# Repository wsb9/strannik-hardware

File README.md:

Hardware sources of Strannik, ortholinear wireless keyboard.

ZMK config is in [peer software repo](https://github.com/wsb9/strannik).

# About

This project inspired by awesome [ZSA Moonlander](https://www.zsa.io/moonlander). 
At the time of start, ZSA guys haven't yet made Voyager, and I wanted very similar 
low profile wireless keyboard, so, this project had a great initial kick.

It currently uses Kailh Choc low profile switches, [NiceNano](https://nicekeyboards.com/nice-nano) as its brain and [ZMK](https://zmk.dev/) as firmware.

Current plan is to make project usable in daily use (instead of cardboard wired prototype).

# Future plans

There's few ideas:

 - make even thinner keeb based on Kailh notebook switches
 - create version with large batteries and backlight
 - probably create version with encoder on the edge

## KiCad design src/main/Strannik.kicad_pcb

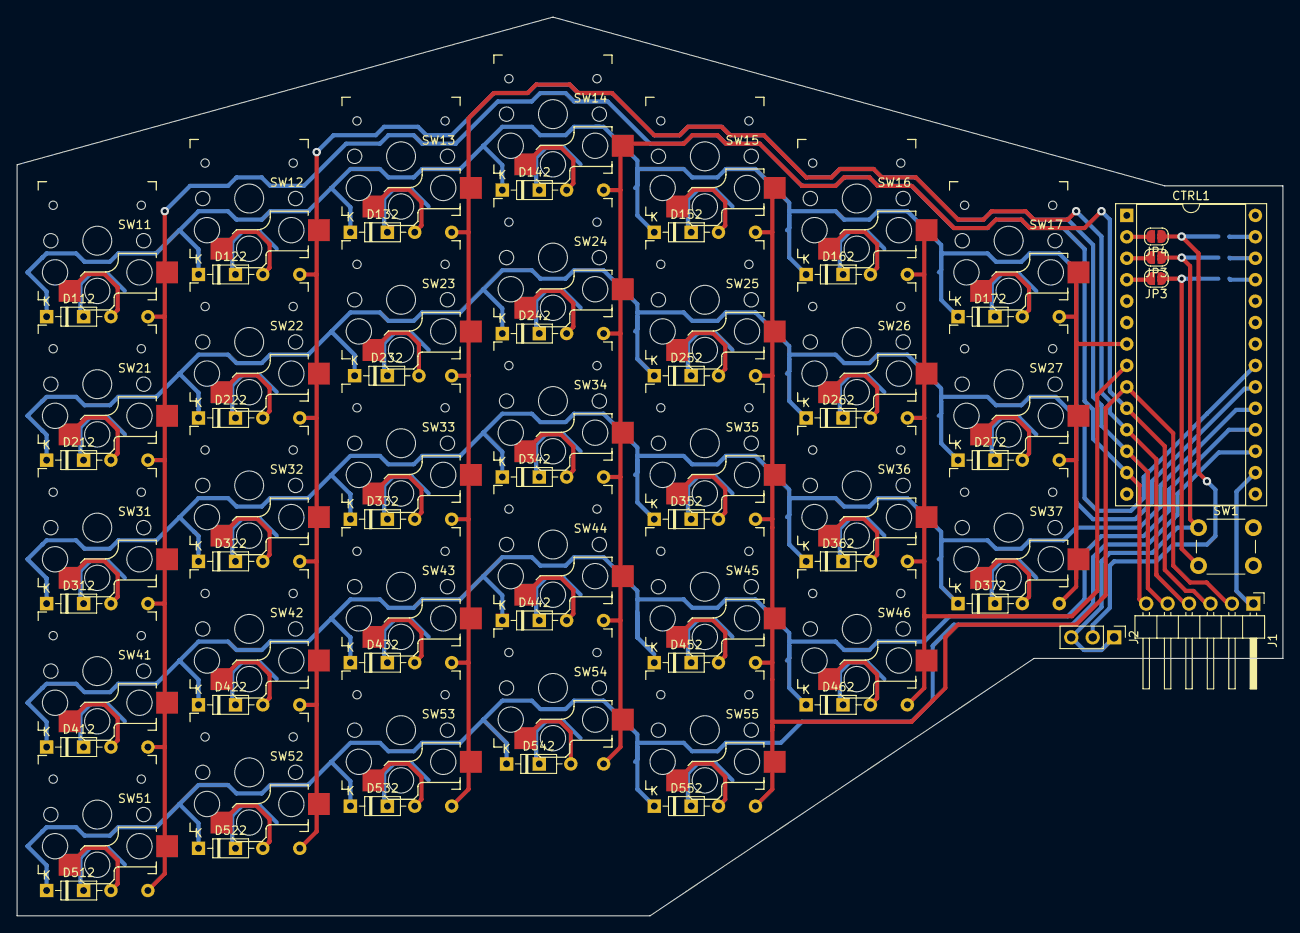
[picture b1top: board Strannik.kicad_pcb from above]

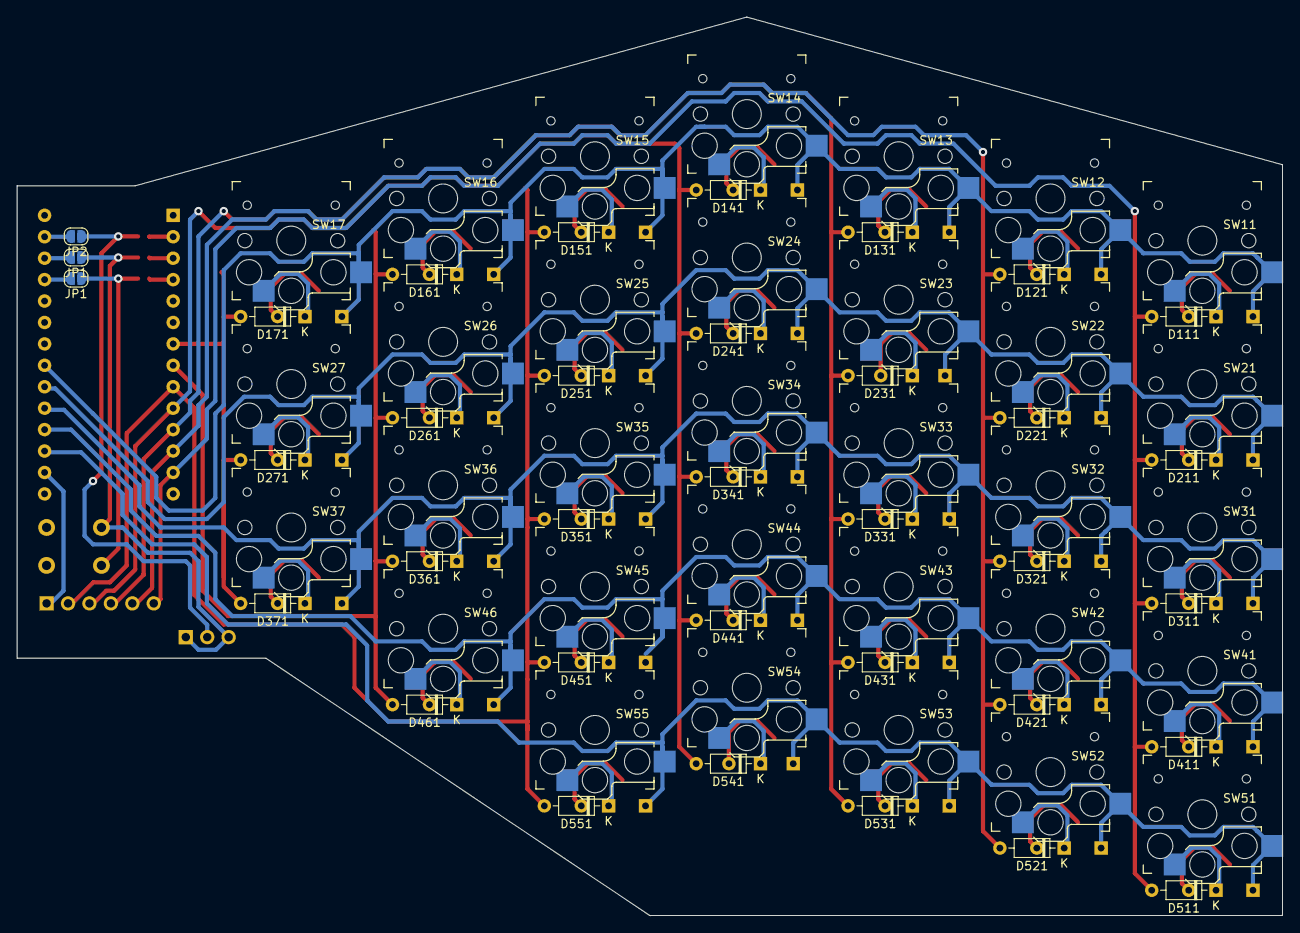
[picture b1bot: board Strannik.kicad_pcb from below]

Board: 2 copper layers, 150.0 x 106.5 mm, 106 parts (35 on the bottom side), 85 nets.

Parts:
CTRL1: Nice Nano; DIP-28_W15.24mm_Socket
D111, D112, D121, D122, D131, D132, D141, D142, D151, D152, D161, D162, D171, D172, D211, D212, D221, D222, D231, D232, D241, D242, D251, D252, D261, D262, D271, D272, D311, D312, D321, D322, D331, D332, D341, D342, D351, D352, D361, D362, D371, D372, D411, D412, D421, D422, D431, D432, D441, D442, D451, D452, D461, D462, D511, D512, D521, D522, D531, D532, D541, D542, D551, D552: 1N4148; D_DO-35_SOD27_P7.62mm_Horizontal
J1: Thumb cluster; PinHeader_1x06_P2.54mm_Horizontal
J2: Battery; PinHeader_1x03_P2.54mm_Vertical
JP1, JP1#2: Ground Left; SolderJumper-2_P1.3mm_Open_RoundedPad1.0x1.5mm
JP2: VCC Left; SolderJumper-2_P1.3mm_Open_RoundedPad1.0x1.5mm
JP3, JP3#2: Ground Right; SolderJumper-2_P1.3mm_Open_RoundedPad1.0x1.5mm
JP4: VCC Right; SolderJumper-2_P1.3mm_Open_RoundedPad1.0x1.5mm
SW1: Reset; SW_PUSH_6mm_H4.3mm
SW11, SW12, SW13, SW14, SW15, SW16, SW17, SW21, SW22, SW23, SW24, SW25, SW26, SW27, SW31, SW32, SW33, SW34, SW35, SW36, SW37, SW41, SW42, SW43, SW44, SW45, SW46, SW51, SW52, SW53, SW54, SW55: SW_Push_Dual; Kailh_socket_PG1350_reversible

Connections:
unnamed: CTRL1.2, JP4.2 (B)
unnamed: CTRL1.3, JP3.2 (B)
unnamed: CTRL1.4, JP3#2.2 (B)
unnamed: CTRL1.7, D171.2 (A), D271.2 (A), D371.2 (A), SW17.4, SW27.4, SW37.4
unnamed: CTRL1.8, D161.2 (A), D261.2 (A), D361.2 (A), D461.2 (A), SW16.4, SW26.4, SW36.4, SW46.4
unnamed: CTRL1.9, D151.2 (A), D251.2 (A), D351.2 (A), D451.2 (A), D551.2 (A), J1.2, SW15.4, SW25.4, SW35.4, SW45.4, SW55.4
unnamed: CTRL1.10, D141.2 (A), D241.2 (A), D341.2 (A), D441.2 (A), D541.2 (A), J1.3, SW14.4, SW24.4, SW34.4, SW44.4, SW54.4
unnamed: CTRL1.11, D131.2 (A), D231.2 (A), D331.2 (A), D431.2 (A), D531.2 (A), J1.4, SW13.4, SW23.4, SW33.4, SW43.4, SW53.4
unnamed: CTRL1.12, D121.2 (A), D221.2 (A), D321.2 (A), D421.2 (A), D521.2 (A), J1.5, SW12.4, SW22.4, SW32.4, SW42.4, SW52.4
unnamed: CTRL1.13, D111.2 (A), D211.2 (A), D311.2 (A), D411.2 (A), D511.2 (A), J1.6, SW11.4, SW21.4, SW31.4, SW41.4, SW51.4
unnamed: CTRL1.16, J1.1
unnamed: CTRL1.17, D512.1 (K), D522.1 (K), D532.1 (K), D542.1 (K), D552.1 (K), SW51.2, SW52.2, SW53.2, SW54.2, SW55.2
unnamed: CTRL1.18, D412.1 (K), D422.1 (K), D432.1 (K), D442.1 (K), D452.1 (K), D462.1 (K), SW41.2, SW42.2, SW43.2, SW44.2, SW45.2, SW46.2
unnamed: CTRL1.19, D312.1 (K), D322.1 (K), D332.1 (K), D342.1 (K), D352.1 (K), D362.1 (K), D372.1 (K), SW31.2, SW32.2, SW33.2, SW34.2, SW35.2, SW36.2, SW37.2
unnamed: CTRL1.20, D212.1 (K), D222.1 (K), D232.1 (K), D242.1 (K), D252.1 (K), D262.1 (K), D272.1 (K), SW21.2, SW22.2, SW23.2, SW24.2, SW25.2, SW26.2, SW27.2
unnamed: CTRL1.21, D112.1 (K), D122.1 (K), D132.1 (K), D142.1 (K), D152.1 (K), D162.1 (K), D172.1 (K), SW11.2, SW12.2, SW13.2, SW14.2, SW15.2, SW16.2, SW17.2
unnamed: CTRL1.25, JP1#2.1 (A), JP1#2.2 (B), JP3#2.1 (A), SW1.2
unnamed: CTRL1.26, JP1.2 (B)
unnamed: CTRL1.27, JP2.2 (B)
unnamed: D111.1 (K), SW11.1
unnamed: D112.2 (A), SW11.3
unnamed: D121.1 (K), SW12.1
unnamed: D122.2 (A), SW12.3
unnamed: D131.1 (K), SW13.1
unnamed: D132.2 (A), SW13.3
unnamed: D141.1 (K), SW14.1
unnamed: D142.2 (A), SW14.3
unnamed: D151.1 (K), SW15.1
unnamed: D152.2 (A), SW15.3
unnamed: D161.1 (K), SW16.1
unnamed: D162.2 (A), SW16.3
unnamed: D171.1 (K), SW17.1
unnamed: D172.2 (A), SW17.3
unnamed: D211.1 (K), SW21.1
unnamed: D212.2 (A), SW21.3
unnamed: D221.1 (K), SW22.1
unnamed: D222.2 (A), SW22.3
unnamed: D231.1 (K), SW23.1
unnamed: D232.2 (A), SW23.3
unnamed: D241.1 (K), SW24.1
unnamed: D242.2 (A), SW24.3
unnamed: D251.1 (K), SW25.1
unnamed: D252.2 (A), SW25.3
unnamed: D261.1 (K), SW26.1
unnamed: D262.2 (A), SW26.3
unnamed: D271.1 (K), SW27.1
unnamed: D272.2 (A), SW27.3
unnamed: D311.1 (K), SW31.1
unnamed: D312.2 (A), SW31.3
unnamed: D321.1 (K), SW32.1
unnamed: D322.2 (A), SW32.3
unnamed: D331.1 (K), SW33.1
unnamed: D332.2 (A), SW33.3
unnamed: D341.1 (K), SW34.1
unnamed: D342.2 (A), SW34.3
unnamed: D351.1 (K), SW35.1
unnamed: D352.2 (A), SW35.3
unnamed: D361.1 (K), SW36.1
unnamed: D362.2 (A), SW36.3
unnamed: D371.1 (K), SW37.1
unnamed: D372.2 (A), SW37.3
unnamed: D411.1 (K), SW41.1
unnamed: D412.2 (A), SW41.3
unnamed: D421.1 (K), SW42.1
unnamed: D422.2 (A), SW42.3
unnamed: D431.1 (K), SW43.1
unnamed: D432.2 (A), SW43.3
unnamed: D441.1 (K), SW44.1
unnamed: D442.2 (A), SW44.3
unnamed: D451.1 (K), SW45.1
unnamed: D452.2 (A), SW45.3
unnamed: D461.1 (K), SW46.1
unnamed: D462.2 (A), SW46.3
unnamed: D511.1 (K), SW51.1
unnamed: D512.2 (A), SW51.3
unnamed: D521.1 (K), SW52.1
unnamed: D522.2 (A), SW52.3
unnamed: D531.1 (K), SW53.1
unnamed: D532.2 (A), SW53.3
unnamed: D541.1 (K), SW54.1
unnamed: D542.2 (A), SW54.3
unnamed: D551.1 (K), SW55.1
unnamed: D552.2 (A), SW55.3
unnamed: J2.1, J2.3, JP1.1 (A), JP3.1 (A), SW1.1
unnamed: J2.2, JP2.1 (A), JP4.1 (A)

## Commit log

2024-05-03 initial version of main pcb
2024-05-05 Layout improvements for main pcb
    * increased column stagger by 1mm
    * tightened switch placement inside column by 1mm, following cap size
    * tightened copper on board, making it 5mm smaller vertically
2024-05-06 new beautiful main board design
2024-05-06 Added README.md
